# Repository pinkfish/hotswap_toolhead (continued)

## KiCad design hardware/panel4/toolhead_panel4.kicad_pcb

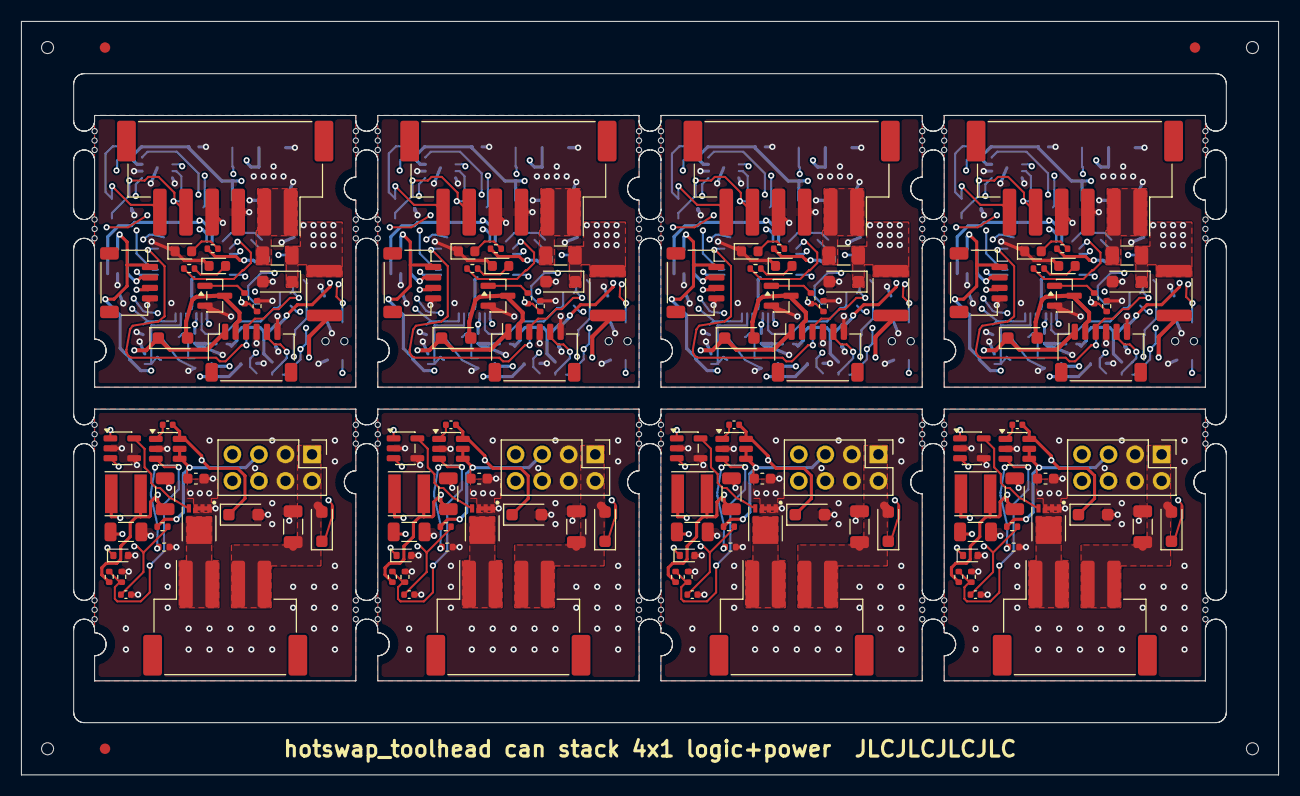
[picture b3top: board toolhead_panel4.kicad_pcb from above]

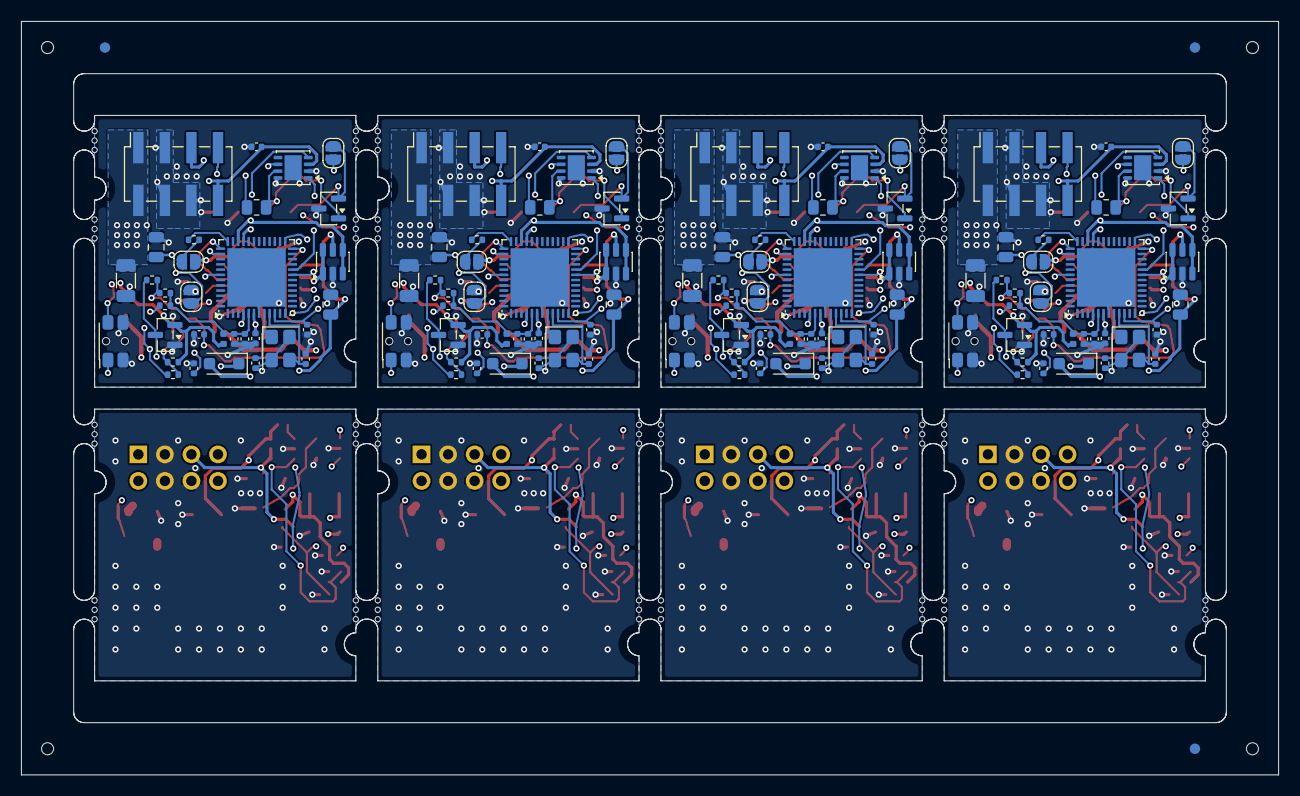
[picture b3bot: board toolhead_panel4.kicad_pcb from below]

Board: 4 copper layers, 120.3 x 72.1 mm, 366 parts (131 on the bottom side), 172 nets.

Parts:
C1_0, C1_2, C1_4, C1_6, C2_1, C2_3, C2_5, C2_7, C4_1, C4_3, C4_5, C4_7: 10uF 50V X5R; C_1206_3216Metric
C5_1, C5_3, C5_5, C5_7: 100nF; C_0603_1608Metric
C6_1, C6_3, C6_5, C6_7, C9_0, C9_2, C9_4, C9_6, C12_0, C12_2, C12_4, C12_6, C15_0, C15_2, C15_4, C15_6, C16_0, C16_2, C16_4, C16_6, C19_0, C19_2, C19_4, C19_6, C20_0, C20_2, C20_4, C20_6: 100nF; C_0402_1005Metric
C8_1, C8_3, C8_5, C8_7: 22uF 25V X5R; C_1206_3216Metric
C10_0, C10_2, C10_4, C10_6, C17_0, C17_2, C17_4, C17_6: 10uF 25V X5R; C_0805_2012Metric
C11_0, C11_2, C11_4, C11_6, C21_1, C21_3, C21_5, C21_7: 1uF; C_0402_1005Metric
C13_0, C13_2, C13_4, C13_6, C14_0, C14_2, C14_4, C14_6: 33pF C0G; C_0402_1005Metric
D1_0, D1_2, D1_4, D1_6: SMF33CA; D_SOD-123F
D3_0, D3_2, D3_4, D3_6, D5_0, D5_2, D5_4, D5_6, D7_1, D7_3, D7_5, D7_7, D9_1, D9_3, D9_5, D9_7: DSK110 100V 1A; D_SOD-123F
D4_0, D4_2, D4_4, D4_6: NUP2105L; SOT-23
D6_0, D6_2, D6_4, D6_6: BAT54S; SOT-23
D10_1, D10_3, D10_5, D10_7: BZX585-C12 12V; D_SOD-523
F1_0, F1_2, F1_4, F1_6: 8A 1206 fuse (0458008.DR); Fuse_1206_3216Metric
F2_0, F2_2, F2_4, F2_6: PTC 0.75A 33V (JK-mSMD075-33); Fuse_1812_4532Metric
FB1_0, FB1_2, FB1_4, FB1_6: 600R@100MHz; L_0402_1005Metric
J1_0, J1_2, J1_4, J1_6: 24V/CAN in (JST XH 1x6 S6B-XH-SM4-TB); JST_XH_S6B-XH-SM4-TB_1x06-1MP_P2.50mm_Horizontal
J2_0, J2_2, J2_4, J2_6: Fan/therm/sensor (JST SH 1x6 SM06B-SRSS-TB); JST_SH_SM06B-SRSS-TB_1x06-1MP_P1.00mm_Horizontal
J3_1, J3_3, J3_5, J3_7: Heater (JST XH 1x4 S4B-XH-SM4-TB); JST_XH_S4B-XH-SM4-TB_1x04-1MP_P2.50mm_Horizontal
J5_0, J5_2, J5_4, J5_6: USB (JST SH 1x4 SM04B-SRSS-TB); JST_SH_SM04B-SRSS-TB_1x04-1MP_P1.00mm_Horizontal
J6_0, J6_2, J6_4, J6_6: Link socket 2x4 (HC-PM254-8.5H-2x4PS); PinSocket_2x04_P2.54mm_Vertical_SMD
J7_1, J7_3, J7_5, J7_7: Link header 2x4 (HX PZ2.54-2x4P ZZ); PinHeader_2x04_P2.54mm_Vertical
JP1_0, JP1_2, JP1_4, JP1_6: TERM; SolderJumper-2_P1.3mm_Open_RoundedPad1.0x1.5mm
JP2_0, JP2_2, JP2_4, JP2_6: NTC/PT1000; SolderJumper-2_P1.3mm_Open_RoundedPad1.0x1.5mm
JP3_0, JP3_2, JP3_4, JP3_6: BOOT; SolderJumper-2_P1.3mm_Open_RoundedPad1.0x1.5mm
KiKit_FID_B_1, KiKit_FID_B_2, KiKit_FID_B_3: Fiducial
KiKit_FID_T_1, KiKit_FID_T_2, KiKit_FID_T_3: Fiducial
KiKit_MB_1_1, KiKit_MB_1_2, KiKit_MB_1_3, KiKit_MB_2_1, KiKit_MB_2_2, KiKit_MB_2_3, KiKit_MB_3_1, KiKit_MB_3_2, KiKit_MB_3_3, KiKit_MB_4_1, KiKit_MB_4_2, KiKit_MB_4_3, KiKit_MB_5_1, KiKit_MB_5_2, KiKit_MB_5_3, KiKit_MB_6_1, KiKit_MB_6_2, KiKit_MB_6_3, KiKit_MB_7_1, KiKit_MB_7_2, KiKit_MB_7_3, KiKit_MB_8_1, KiKit_MB_8_2, KiKit_MB_8_3, KiKit_MB_9_1, KiKit_MB_9_2, KiKit_MB_9_3, KiKit_MB_10_1, KiKit_MB_10_2, KiKit_MB_10_3, KiKit_MB_11_1, KiKit_MB_11_2, KiKit_MB_11_3, KiKit_MB_12_1, KiKit_MB_12_2, KiKit_MB_12_3, KiKit_MB_13_1, KiKit_MB_13_2, KiKit_MB_13_3, KiKit_MB_14_1, KiKit_MB_14_2, KiKit_MB_14_3, KiKit_MB_15_1, KiKit_MB_15_2, KiKit_MB_15_3, KiKit_MB_16_1, KiKit_MB_16_2, KiKit_MB_16_3, KiKit_MB_17_1, KiKit_MB_17_2, KiKit_MB_17_3, KiKit_MB_18_1, KiKit_MB_18_2, KiKit_MB_18_3, KiKit_MB_19_1, KiKit_MB_19_2, KiKit_MB_19_3, KiKit_MB_20_1, KiKit_MB_20_2, KiKit_MB_20_3, KiKit_MB_21_1, KiKit_MB_21_2, KiKit_MB_21_3, KiKit_MB_22_1, KiKit_MB_22_2, KiKit_MB_22_3, KiKit_MB_23_1, KiKit_MB_23_2, KiKit_MB_23_3, KiKit_MB_24_1, KiKit_MB_24_2, KiKit_MB_24_3, KiKit_MB_25_1, KiKit_MB_25_2, KiKit_MB_25_3, KiKit_MB_26_1, KiKit_MB_26_2, KiKit_MB_26_3, KiKit_MB_27_1, KiKit_MB_27_2, KiKit_MB_27_3, KiKit_MB_28_1, KiKit_MB_28_2, KiKit_MB_28_3, KiKit_MB_29_1, KiKit_MB_29_2, KiKit_MB_29_3, KiKit_MB_30_1, KiKit_MB_30_2, KiKit_MB_30_3, KiKit_MB_31_1, KiKit_MB_31_2, KiKit_MB_31_3, KiKit_MB_32_1, KiKit_MB_32_2, KiKit_MB_32_3: NPTH
KiKit_TO_1, KiKit_TO_2, KiKit_TO_3, KiKit_TO_4: NPTH
L1_1, L1_3, L1_5, L1_7: 22uH 1.2A (FNR4030S220MT); L_Taiyo-Yuden_NR-40xx
LED1_0, LED1_2, LED1_4, LED1_6: yellow-green; LED_0603_1608Metric
LED2_0, LED2_2, LED2_4, LED2_6: blue; LED_0603_1608Metric
Q2_1, Q2_3, Q2_5, Q2_7: AON7264E; AOS_DFN-8-1EP_3x3mm_P0.65mm
Q3_0, Q3_2, Q3_4, Q3_6: WST6066A; SOT-23
R2_1, R2_3, R2_5, R2_7: 33k; R_0402_1005Metric
R3_1, R3_3, R3_5, R3_7, R13_1, R13_3, R13_5, R13_7, R14_1, R14_3, R14_5, R14_7, R16_0, R16_2, R16_4, R16_6, R22_0, R22_2, R22_4, R22_6: 10k; R_0402_1005Metric
R4_0, R4_2, R4_4, R4_6, R5_0, R5_2, R5_4, R5_6, R15_0, R15_2, R15_4, R15_6, R19_0, R19_2, R19_4, R19_6, R23_0, R23_2, R23_4, R23_6: 1k; R_0402_1005Metric
R6_0, R6_2, R6_4, R6_6: 100R; R_0402_1005Metric
R11_0, R11_2, R11_4, R11_6: 120R; R_0805_2012Metric
R17_0, R17_2, R17_4, R17_6: 4.7k 0.1% 25ppm; R_0402_1005Metric
R18_0, R18_2, R18_4, R18_6: 4.12k 0.1% 25ppm; R_0402_1005Metric
SW1_0, SW1_2, SW1_4, SW1_6: RESET; SW_SPST_EVQP7C
U1_1, U1_3, U1_5, U1_7: LMR16006XDDC; SOT-23-6
U3_0, U3_2, U3_4, U3_6: TCAN3414DRBR; VSON-8-1EP_3x3mm_P0.65mm_EP1.65x2.4mm
U5_0, U5_2, U5_4, U5_6: USBLC6-2SC6; SOT-23-6
U6_0, U6_2, U6_4, U6_6: STM32G0B1CEU6; QFN-48-1EP_7x7mm_P0.5mm_EP5.6x5.6mm
U7_1, U7_3, U7_5, U7_7: UCC27517DBVR; SOT-23-5
Y1_0, Y1_2, Y1_4, Y1_6: 8MHz 20pF 3225; Crystal_SMD_3225-4Pin_3.2x2.5mm

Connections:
Board_0-/+3V3: C9_0.1, C10_0.1, C16_0.1, D6_0.2 (K2), FB1_0.1, J6_0.8, JP3_0.1, R5_0.1, R22_0.1, U3_0.3, U6_0.4, U6_0.6
Board_0-/+24V: C1_0.1, D1_0.1, F1_0.2, F2_0.1, J6_0.1, J6_0.2
Board_0-/BOOT_SW: JP3_0.2, R4_0.1
Board_0-/CAN_H: D4_0.1, J1_0.5, R11_0.1, U3_0.7
Board_0-/CAN_L: D4_0.2, J1_0.6, JP1_0.2, U3_0.6
Board_0-/CAN_RX: U3_0.4, U6_0.19
Board_0-/CAN_TERM: JP1_0.1, R11_0.2
Board_0-/CAN_TX: U3_0.1, U6_0.20
Board_0-/FAN_G: Q3_0.1, R15_0.2
Board_0-/FAN_N: D5_0.2, J2_0.2, Q3_0.3
Board_0-/FAN_P: D5_0.1, F2_0.2, J2_0.1
Board_0-/FAN_PWM: R15_0.1, R16_0.1, U6_0.25
Board_0-/GND: C1_0.2, C9_0.2, C10_0.2, C11_0.2, C12_0.2, C13_0.2, C14_0.2, C15_0.2, C16_0.2, C17_0.2, C19_0.2, C20_0.2, D1_0.2, D4_0.3, D6_0.1 (A1), J1_0.3, J1_0.4, J2_0.4, J2_0.6, J5_0.4, J6_0.3, J6_0.4, J6_0.6, LED1_0.1 (K), LED2_0.1 (K), Q3_0.2, R16_0.2, SW1_0.2, U3_0.2, U3_0.8, U3_0.9, U5_0.2 (GND), U6_0.7, U6_0.49, Y1_0.2, Y1_0.4
Board_0-/HEAT_PWM: J6_0.7, U6_0.38
Board_0-/JP2_A: JP2_0.2, R18_0.2
Board_0-/LED1_A: LED1_0.2 (A), R5_0.2
Board_0-/LED2_A: LED2_0.2 (A), R6_0.2
Board_0-/LED_STAT: R6_0.1, U6_0.37
Board_0-/NRST: C15_0.1, SW1_0.1, U6_0.10
Board_0-/OSC_IN: C13_0.1, U6_0.8, Y1_0.1
Board_0-/OSC_OUT: C14_0.1, U6_0.9, Y1_0.3
Board_0-/SENS: J2_0.5, R22_0.2, R23_0.1
Board_0-/SENS_IN: C20_0.1, R23_0.2, U6_0.42
Board_0-/SWCLK: R4_0.2, U6_0.36
Board_0-/TH_ADC: C19_0.1, D6_0.3 (K1/A2), R19_0.2, U6_0.24
Board_0-/TH_SIG: J2_0.3, JP2_0.1, R17_0.2, R19_0.1
Board_0-/USB_D_N: J5_0.2, U5_0.1 (IO1), U5_0.6 (IO1), U6_0.33
Board_0-/USB_D_P: J5_0.3, U5_0.3 (IO2), U5_0.4 (IO2), U6_0.34
Board_0-/VBUS: C17_0.1, D3_0.2, J5_0.1, U5_0.5 (VBUS)
Board_0-/VIN_LOGIC: D3_0.1, J6_0.5
Board_0-/VIN_RAW: F1_0.1, J1_0.1, J1_0.2
Board_0-/VREFP: C11_0.1, C12_0.1, FB1_0.2, R17_0.1, R18_0.1, U6_0.5
Board_1-/+3V3: C8_1.1, J7_1.8, L1_1.2, R2_1.1
Board_1-/+24V: C2_1.1, D7_1.2, J3_1.3, J3_1.4, J7_1.1, J7_1.2
Board_1-/BUCK_BOOT: C6_1.1, U1_1.1
Board_1-/BUCK_FB: R2_1.2, R3_1.1, U1_1.3
Board_1-/BUCK_SW: C6_1.2, D9_1.1, L1_1.1, U1_1.6
Board_1-/GATE_12V: C21_1.1, D10_1.1, R13_1.2, U7_1.1
Board_1-/GND: C2_1.2, C4_1.2, C5_1.2, C8_1.2, C21_1.2, D9_1.2, D10_1.2, J7_1.3, J7_1.4, J7_1.6, Q2_1.1, Q2_1.2, Q2_1.3, R3_1.2, R14_1.2, U1_1.2, U7_1.2, U7_1.4
Board_1-/HEAT_G: Q2_1.4, U7_1.5
Board_1-/HEAT_N: J3_1.1, J3_1.2, Q2_1.5
Board_1-/HEAT_PWM: J7_1.7, R14_1.1, U7_1.3
Board_1-/VIN_LOGIC: C4_1.1, C5_1.1, D7_1.1, J7_1.5, R13_1.1, U1_1.4, U1_1.5
Board_2-/+3V3: C9_2.1, C10_2.1, C16_2.1, D6_2.2 (K2), FB1_2.1, J6_2.8, JP3_2.1, R5_2.1, R22_2.1, U3_2.3, U6_2.4, U6_2.6
Board_2-/+24V: C1_2.1, D1_2.1, F1_2.2, F2_2.1, J6_2.1, J6_2.2
Board_2-/BOOT_SW: JP3_2.2, R4_2.1
Board_2-/CAN_H: D4_2.1, J1_2.5, R11_2.1, U3_2.7
Board_2-/CAN_L: D4_2.2, J1_2.6, JP1_2.2, U3_2.6
Board_2-/CAN_RX: U3_2.4, U6_2.19
Board_2-/CAN_TERM: JP1_2.1, R11_2.2
Board_2-/CAN_TX: U3_2.1, U6_2.20
Board_2-/FAN_G: Q3_2.1, R15_2.2
Board_2-/FAN_N: D5_2.2, J2_2.2, Q3_2.3
Board_2-/FAN_P: D5_2.1, F2_2.2, J2_2.1
Board_2-/FAN_PWM: R15_2.1, R16_2.1, U6_2.25
Board_2-/GND: C1_2.2, C9_2.2, C10_2.2, C11_2.2, C12_2.2, C13_2.2, C14_2.2, C15_2.2, C16_2.2, C17_2.2, C19_2.2, C20_2.2, D1_2.2, D4_2.3, D6_2.1 (A1), J1_2.3, J1_2.4, J2_2.4, J2_2.6, J5_2.4, J6_2.3, J6_2.4, J6_2.6, LED1_2.1 (K), LED2_2.1 (K), Q3_2.2, R16_2.2, SW1_2.2, U3_2.2, U3_2.8, U3_2.9, U5_2.2 (GND), U6_2.7, U6_2.49, Y1_2.2, Y1_2.4
Board_2-/HEAT_PWM: J6_2.7, U6_2.38
Board_2-/JP2_A: JP2_2.2, R18_2.2
Board_2-/LED1_A: LED1_2.2 (A), R5_2.2
Board_2-/LED2_A: LED2_2.2 (A), R6_2.2
Board_2-/LED_STAT: R6_2.1, U6_2.37
Board_2-/NRST: C15_2.1, SW1_2.1, U6_2.10
Board_2-/OSC_IN: C13_2.1, U6_2.8, Y1_2.1
Board_2-/OSC_OUT: C14_2.1, U6_2.9, Y1_2.3
Board_2-/SENS: J2_2.5, R22_2.2, R23_2.1
Board_2-/SENS_IN: C20_2.1, R23_2.2, U6_2.42
Board_2-/SWCLK: R4_2.2, U6_2.36
Board_2-/TH_ADC: C19_2.1, D6_2.3 (K1/A2), R19_2.2, U6_2.24
Board_2-/TH_SIG: J2_2.3, JP2_2.1, R17_2.2, R19_2.1
Board_2-/USB_D_N: J5_2.2, U5_2.1 (IO1), U5_2.6 (IO1), U6_2.33
Board_2-/USB_D_P: J5_2.3, U5_2.3 (IO2), U5_2.4 (IO2), U6_2.34
Board_2-/VBUS: C17_2.1, D3_2.2, J5_2.1, U5_2.5 (VBUS)
Board_2-/VIN_LOGIC: D3_2.1, J6_2.5
Board_2-/VIN_RAW: F1_2.1, J1_2.1, J1_2.2
Board_2-/VREFP: C11_2.1, C12_2.1, FB1_2.2, R17_2.1, R18_2.1, U6_2.5
Board_3-/+3V3: C8_3.1, J7_3.8, L1_3.2, R2_3.1
Board_3-/+24V: C2_3.1, D7_3.2, J3_3.3, J3_3.4, J7_3.1, J7_3.2
Board_3-/BUCK_BOOT: C6_3.1, U1_3.1
Board_3-/BUCK_FB: R2_3.2, R3_3.1, U1_3.3
Board_3-/BUCK_SW: C6_3.2, D9_3.1, L1_3.1, U1_3.6
Board_3-/GATE_12V: C21_3.1, D10_3.1, R13_3.2, U7_3.1
Board_3-/GND: C2_3.2, C4_3.2, C5_3.2, C8_3.2, C21_3.2, D9_3.2, D10_3.2, J7_3.3, J7_3.4, J7_3.6, Q2_3.1, Q2_3.2, Q2_3.3, R3_3.2, R14_3.2, U1_3.2, U7_3.2, U7_3.4
Board_3-/HEAT_G: Q2_3.4, U7_3.5
Board_3-/HEAT_N: J3_3.1, J3_3.2, Q2_3.5
Board_3-/HEAT_PWM: J7_3.7, R14_3.1, U7_3.3
Board_3-/VIN_LOGIC: C4_3.1, C5_3.1, D7_3.1, J7_3.5, R13_3.1, U1_3.4, U1_3.5
Board_4-/+3V3: C9_4.1, C10_4.1, C16_4.1, D6_4.2 (K2), FB1_4.1, J6_4.8, JP3_4.1, R5_4.1, R22_4.1, U3_4.3, U6_4.4, U6_4.6
Board_4-/+24V: C1_4.1, D1_4.1, F1_4.2, F2_4.1, J6_4.1, J6_4.2
Board_4-/BOOT_SW: JP3_4.2, R4_4.1
Board_4-/CAN_H: D4_4.1, J1_4.5, R11_4.1, U3_4.7
Board_4-/CAN_L: D4_4.2, J1_4.6, JP1_4.2, U3_4.6
Board_4-/CAN_RX: U3_4.4, U6_4.19
Board_4-/CAN_TERM: JP1_4.1, R11_4.2
Board_4-/CAN_TX: U3_4.1, U6_4.20
Board_4-/FAN_G: Q3_4.1, R15_4.2
Board_4-/FAN_N: D5_4.2, J2_4.2, Q3_4.3
Board_4-/FAN_P: D5_4.1, F2_4.2, J2_4.1
Board_4-/FAN_PWM: R15_4.1, R16_4.1, U6_4.25
Board_4-/GND: C1_4.2, C9_4.2, C10_4.2, C11_4.2, C12_4.2, C13_4.2, C14_4.2, C15_4.2, C16_4.2, C17_4.2, C19_4.2, C20_4.2, D1_4.2, D4_4.3, D6_4.1 (A1), J1_4.3, J1_4.4, J2_4.4, J2_4.6, J5_4.4, J6_4.3, J6_4.4, J6_4.6, LED1_4.1 (K), LED2_4.1 (K), Q3_4.2, R16_4.2, SW1_4.2, U3_4.2, U3_4.8, U3_4.9, U5_4.2 (GND), U6_4.7, U6_4.49, Y1_4.2, Y1_4.4
Board_4-/HEAT_PWM: J6_4.7, U6_4.38
Board_4-/JP2_A: JP2_4.2, R18_4.2
Board_4-/LED1_A: LED1_4.2 (A), R5_4.2
Board_4-/LED2_A: LED2_4.2 (A), R6_4.2
Board_4-/LED_STAT: R6_4.1, U6_4.37
Board_4-/NRST: C15_4.1, SW1_4.1, U6_4.10
Board_4-/OSC_IN: C13_4.1, U6_4.8, Y1_4.1
Board_4-/OSC_OUT: C14_4.1, U6_4.9, Y1_4.3
Board_4-/SENS: J2_4.5, R22_4.2, R23_4.1
Board_4-/SENS_IN: C20_4.1, R23_4.2, U6_4.42
Board_4-/SWCLK: R4_4.2, U6_4.36
Board_4-/TH_ADC: C19_4.1, D6_4.3 (K1/A2), R19_4.2, U6_4.24
Board_4-/TH_SIG: J2_4.3, JP2_4.1, R17_4.2, R19_4.1
Board_4-/USB_D_N: J5_4.2, U5_4.1 (IO1), U5_4.6 (IO1), U6_4.33
Board_4-/USB_D_P: J5_4.3, U5_4.3 (IO2), U5_4.4 (IO2), U6_4.34
Board_4-/VBUS: C17_4.1, D3_4.2, J5_4.1, U5_4.5 (VBUS)
Board_4-/VIN_LOGIC: D3_4.1, J6_4.5
Board_4-/VIN_RAW: F1_4.1, J1_4.1, J1_4.2
Board_4-/VREFP: C11_4.1, C12_4.1, FB1_4.2, R17_4.1, R18_4.1, U6_4.5
Board_5-/+3V3: C8_5.1, J7_5.8, L1_5.2, R2_5.1
Board_5-/+24V: C2_5.1, D7_5.2, J3_5.3, J3_5.4, J7_5.1, J7_5.2
Board_5-/BUCK_BOOT: C6_5.1, U1_5.1
Board_5-/BUCK_FB: R2_5.2, R3_5.1, U1_5.3
Board_5-/BUCK_SW: C6_5.2, D9_5.1, L1_5.1, U1_5.6
Board_5-/GATE_12V: C21_5.1, D10_5.1, R13_5.2, U7_5.1
Board_5-/GND: C2_5.2, C4_5.2, C5_5.2, C8_5.2, C21_5.2, D9_5.2, D10_5.2, J7_5.3, J7_5.4, J7_5.6, Q2_5.1, Q2_5.2, Q2_5.3, R3_5.2, R14_5.2, U1_5.2, U7_5.2, U7_5.4
Board_5-/HEAT_G: Q2_5.4, U7_5.5
Board_5-/HEAT_N: J3_5.1, J3_5.2, Q2_5.5
Board_5-/HEAT_PWM: J7_5.7, R14_5.1, U7_5.3
Board_5-/VIN_LOGIC: C4_5.1, C5_5.1, D7_5.1, J7_5.5, R13_5.1, U1_5.4, U1_5.5
Board_6-/+3V3: C9_6.1, C10_6.1, C16_6.1, D6_6.2 (K2), FB1_6.1, J6_6.8, JP3_6.1, R5_6.1, R22_6.1, U3_6.3, U6_6.4, U6_6.6
Board_6-/+24V: C1_6.1, D1_6.1, F1_6.2, F2_6.1, J6_6.1, J6_6.2
Board_6-/BOOT_SW: JP3_6.2, R4_6.1
Board_6-/CAN_H: D4_6.1, J1_6.5, R11_6.1, U3_6.7
Board_6-/CAN_L: D4_6.2, J1_6.6, JP1_6.2, U3_6.6
Board_6-/CAN_RX: U3_6.4, U6_6.19
Board_6-/CAN_TERM: JP1_6.1, R11_6.2
Board_6-/CAN_TX: U3_6.1, U6_6.20
Board_6-/FAN_G: Q3_6.1, R15_6.2
Board_6-/FAN_N: D5_6.2, J2_6.2, Q3_6.3
Board_6-/FAN_P: D5_6.1, F2_6.2, J2_6.1
Board_6-/FAN_PWM: R15_6.1, R16_6.1, U6_6.25
Board_6-/GND: C1_6.2, C9_6.2, C10_6.2, C11_6.2, C12_6.2, C13_6.2, C14_6.2, C15_6.2, C16_6.2, C17_6.2, C19_6.2, C20_6.2, D1_6.2, D4_6.3, D6_6.1 (A1), J1_6.3, J1_6.4, J2_6.4, J2_6.6, J5_6.4, J6_6.3, J6_6.4, J6_6.6, LED1_6.1 (K), LED2_6.1 (K), Q3_6.2, R16_6.2, SW1_6.2, U3_6.2, U3_6.8, U3_6.9, U5_6.2 (GND), U6_6.7, U6_6.49, Y1_6.2, Y1_6.4
Board_6-/HEAT_PWM: J6_6.7, U6_6.38
Board_6-/JP2_A: JP2_6.2, R18_6.2
Board_6-/LED1_A: LED1_6.2 (A), R5_6.2
Board_6-/LED2_A: LED2_6.2 (A), R6_6.2
Board_6-/LED_STAT: R6_6.1, U6_6.37
Board_6-/NRST: C15_6.1, SW1_6.1, U6_6.10
Board_6-/OSC_IN: C13_6.1, U6_6.8, Y1_6.1
Board_6-/OSC_OUT: C14_6.1, U6_6.9, Y1_6.3
Board_6-/SENS: J2_6.5, R22_6.2, R23_6.1
Board_6-/SENS_IN: C20_6.1, R23_6.2, U6_6.42
Board_6-/SWCLK: R4_6.2, U6_6.36
Board_6-/TH_ADC: C19_6.1, D6_6.3 (K1/A2), R19_6.2, U6_6.24
Board_6-/TH_SIG: J2_6.3, JP2_6.1, R17_6.2, R19_6.1
Board_6-/USB_D_N: J5_6.2, U5_6.1 (IO1), U5_6.6 (IO1), U6_6.33
Board_6-/USB_D_P: J5_6.3, U5_6.3 (IO2), U5_6.4 (IO2), U6_6.34
Board_6-/VBUS: C17_6.1, D3_6.2, J5_6.1, U5_6.5 (VBUS)
Board_6-/VIN_LOGIC: D3_6.1, J6_6.5
Board_6-/VIN_RAW: F1_6.1, J1_6.1, J1_6.2
Board_6-/VREFP: C11_6.1, C12_6.1, FB1_6.2, R17_6.1, R18_6.1, U6_6.5
Board_7-/+3V3: C8_7.1, J7_7.8, L1_7.2, R2_7.1
Board_7-/+24V: C2_7.1, D7_7.2, J3_7.3, J3_7.4, J7_7.1, J7_7.2
Board_7-/BUCK_BOOT: C6_7.1, U1_7.1
Board_7-/BUCK_FB: R2_7.2, R3_7.1, U1_7.3
Board_7-/BUCK_SW: C6_7.2, D9_7.1, L1_7.1, U1_7.6
Board_7-/GATE_12V: C21_7.1, D10_7.1, R13_7.2, U7_7.1
Board_7-/GND: C2_7.2, C4_7.2, C5_7.2, C8_7.2, C21_7.2, D9_7.2, D10_7.2, J7_7.3, J7_7.4, J7_7.6, Q2_7.1, Q2_7.2, Q2_7.3, R3_7.2, R14_7.2, U1_7.2, U7_7.2, U7_7.4
Board_7-/HEAT_G: Q2_7.4, U7_7.5
Board_7-/HEAT_N: J3_7.1, J3_7.2, Q2_7.5
Board_7-/HEAT_PWM: J7_7.7, R14_7.1, U7_7.3
Board_7-/VIN_LOGIC: C4_7.1, C5_7.1, D7_7.1, J7_7.5, R13_7.1, U1_7.4, U1_7.5

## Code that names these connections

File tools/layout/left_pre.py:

"""left_pre.py board.kicad_pcb - pre-route the lines leaving U6's left side, on B.Cu.
TH_ADC (pin 13) and SENS_IN (pin 14) leave side by side and run down parallel lanes past
the crystal cluster, TH_ADC inside, so they never cross:
- TH_ADC drops beside C15/C14 to R19, picks up C19 next to it and, through one via, the
  D6 clamp on top: the filter and clamp stay within a few mm of the pin
- SENS_IN drops one lane further out, turns west under C16 and comes up through a via
  under C20, the switch input's filter cap on top
CAN_TX/CAN_RX run in two more lanes outside SENS_IN's, down past U3's pin column, and
U3's +3V3 pin, boxed in by the CAN lanes, is fed through a via beside it. FAN_PWM
crosses the lanes on F.Cu just below JP1, so U3's CAN pins stay clear.
Runs before planes_fanout so the plane vias land clear of all of these.
"""
import sys

import pcbnew

mm = pcbnew.FromMM
b = pcbnew.LoadBoard(sys.argv[1])
O = 100.0
FP = {f.GetReference(): f for f in b.GetFootprints()}
F, B = pcbnew.F_Cu, pcbnew.B_Cu


def at(ref, num):
    q = [p for p in FP[ref].Pads() if p.GetNumber() == num][0].GetPosition()
    return pcbnew.ToMM(q.x) - O, pcbnew.ToMM(q.y) - O


def pad_net(ref, net):
    p = [p for p in FP[ref].Pads() if p.GetNetname() == net][0].GetPosition()
    return pcbnew.ToMM(p.x) - O, pcbnew.ToMM(p.y) - O


def route(net, layer, *pts):
    for a, c in zip(pts, pts[1:]):
        t = pcbnew.PCB_TRACK(b)
        t.SetStart(pcbnew.VECTOR2I(mm(O + a[0]), mm(O + a[1])))
        t.SetEnd(pcbnew.VECTOR2I(mm(O + c[0]), mm(O + c[1])))
        t.SetWidth(mm(0.2))
        t.SetLayer(layer)
        t.SetNet(b.FindNet(net))
        t.SetLocked(True)
        b.Add(t)


def via(net, x, y):
    v = pcbnew.PCB_VIA(b)
    v.SetPosition(pcbnew.VECTOR2I(mm(O + x), mm(O + y)))
    v.SetWidth(mm(0.6))
    v.SetDrill(mm(0.3))
    v.SetNet(b.FindNet(net))
    v.SetLocked(True)
    b.Add(v)


th, sens = at('U6', '13'), at('U6', '14')
r19, c19, d6 = pad_net('R19', '/TH_ADC'), pad_net('C19', '/TH_ADC'), pad_net('D6', '/TH_ADC')
c20 = pad_net('C20', '/SENS_IN')
# TH_ADC: lane 0.45 mm left of C15's pads, down to R19, C19 alongside, via up to D6
xt = pad_net('C15', '/NRST')[0] - 0.75
route('/TH_ADC', B, th, (xt, th[1]), (xt, r19[1] - 0.6), r19, c19)
vy = d6[1] - 0.75
via('/TH_ADC', xt, vy)
route('/TH_ADC', F, (xt, vy), (xt, d6[1]), d6)
# SENS_IN: lane 0.6 mm further out, west between C16 and C19, up under C20
xs, ys = xt - 0.6, r19[1] - 0.75
xv = c20[0] + 1.6
route('/SENS_IN', B, sens, (xs, sens[1]), (xs, ys), (xv, ys))
via('/SENS_IN', xv, ys)
route('/SENS_IN', F, (xv, ys), (c20[0], ys), c20)
# CAN_TX / CAN_RX: straight across from pins 20/19 and down two lanes between U3's pin
# column and SENS_IN's, TX inside to U3 pin 1, RX outside to pin 4 at the bottom
tx, rx = at('U6', '20'), at('U6', '19')
u3tx, u3rx = pad_net('U3', '/CAN_TX'), pad_net('U3', '/CAN_RX')
xtx, xrx = u3tx[0] + 0.25, xs - 0.55
route('/CAN_TX', B, tx, (xtx, tx[1]), (xtx, u3tx[1] - 0.45), u3tx)
route('/CAN_RX', B, rx, (xrx, rx[1]), (xrx, u3rx[1]), u3rx)          # level with pin 4, clear of pin 3
# +3V3 for U3 pin 3, which sits inside the CAN_TX/CAN_RX loop: a via beside the pin, then
# F.Cu round to D6's +3V3 pad, with a second via down to C16, U3's decoupling cap
p3 = pad_net('U3', '/+3V3')
p3r = max(pcbnew.ToMM(p.GetBoundingBox().GetRight()) for p in FP['U3'].Pads() if p.GetNetname() == '/+3V3') - O
c16, d6v = pad_net('C16', '/+3V3'), pad_net('D6', '/+3V3')
lv = (p3r + 0.51, p3[1])
xt3 = c16[0] + 0.18
route('/+3V3', B, p3, lv)
via('/+3V3', *lv)
route('/+3V3', F, lv, (xt3, lv[1]), (xt3, c16[1] - 0.75), (xt3, d6v[1]), d6v)
via('/+3V3', xt3, c16[1] - 0.75)
route('/+3V3', B, (xt3, c16[1] - 0.75), c16)
# CAN_H / CAN_L at U3: pins 6/7 face H1's keep-out, with one track's width between them,
# and pin 8 (GND) above them. Pins 8 and 2 tie into the exposed pad instead of taking a via;
# CAN_H takes the corridor up and across under D4 to its pad 1, and CAN_L drops through a
# via below pin 5 and runs up on F.Cu to JP1, with a second via down to D4 pad 2
ep = [p for p in FP['U3'].Pads() if p.GetNumber() == ''][0].GetBoundingBox()
epl, epr = pcbnew.ToMM(ep.GetLeft()) - O, pcbnew.ToMM(ep.GetRight()) - O
g8, g2 = at('U3', '8'), at('U3', '2')
route('/GND', B, g8, (epl + 0.2, g8[1]))
route('/GND', B, g2, (epr - 0.2, g2[1]))
ec = ((epl + epr) / 2, pcbnew.ToMM(ep.GetCenter().y) - O)
via('/GND', ec[0] - 0.15, ec[1] + 0.7)    # the pad's plane via, clear of FAN_PWM and the +3V3 feed on top
ch, cl = at('U3', '7'), at('U3', '6')
d4h, d4l, jl2 = pad_net('D4', '/CAN_H'), pad_net('D4', '/CAN_L'), pad_net('JP1', '/CAN_L')
xc = ch[0] - 0.76                          # corridor between the pins and H1's keep-out
yh = d4h[1] + 1.21                         # under D4's pads, above pin 8
route('/CAN_H', B, ch, (xc, ch[1]), (xc, yh), (d4h[0], yh), d4h)
v1 = (xc + 0.11, cl[1] + 1.42)             # below pin 5, clear of C20 on top
route('/CAN_L', B, cl, (xc, cl[1]), (xc, v1[1] - 0.35), v1)
via('/CAN_L', *v1)
v2 = (xc + 0.46, d4l[1] + 0.06)            # beside D4 pad 2
route('/CAN_L', F, v1, (v1[0], jl2[1] + 0.35), (v2[0], jl2[1]), jl2)
route('/CAN_L', F, (v2[0], jl2[1]), v2)
via('/CAN_L', *v2)
route('/CAN_L', B, v2, d4l)
# FAN_PWM: pin 17 sits between the CAN_RX and SENS_IN lanes, which wall U6 off from the
# west on B.Cu. A via just off the pin, then F.Cu down the gap between C1's pads, west under
# C1 and JP1 (crossing all four lanes), down between JP1 and CAN_L's F.Cu run, and west
# above Q3 to R15/R16
fp = at('U6', '17')
r15, r16 = pad_net('R15', '/FAN_PWM'), pad_net('R16', '/FAN_PWM')
c1r = pcbnew.ToMM([p for p in FP['C1'].Pads() if p.GetNetname() == '/+24V'][0].GetBoundingBox().GetRight()) - O
jp = [p.GetBoundingBox() for p in FP['JP1'].Pads()]
jl, jr = (min(pcbnew.ToMM(r.GetLeft()) for r in jp) - O, max(pcbnew.ToMM(r.GetRight()) for r in jp) - O)
jb = max(pcbnew.ToMM(r.GetBottom()) for r in jp) - O
qt = min(pcbnew.ToMM(p.GetBoundingBox().GetTop()) for p in FP['Q3'].Pads()) - O
vf = (fp[0] - 1.06, fp[1] - 0.35)          # 0.3 mm from C1's 24 V pad above, CAN_RX's lane below
xg, y1, xw, yl = c1r + 0.45, jb + 0.3, jl - 0.55, qt - 0.5
route('/FAN_PWM', B, fp, (fp[0] - 0.71, fp[1]), vf)
via('/FAN_PWM', *vf)
route('/FAN_PWM', F, vf, (xg, vf[1]), (xg, y1 - 0.17), (jr + 0.25, y1 - 0.17), (jr + 0.05, y1), (xw, y1), (xw, yl),
      (r15[0] + 1.6, yl), (r15[0] + 1.45, yl - 0.1), (r15[0], yl - 0.1), r15, r16)
pcbnew.SaveBoard(sys.argv[1], b)
print('TH_ADC, SENS_IN, CAN_TX/RX, the U3 CAN_H/CAN_L escape, U3 +3V3 and FAN_PWM pre-routed')

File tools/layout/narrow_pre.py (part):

"""narrow_pre.py board.kicad_pcb - pre-routes for the 27 mm board (run_narrow.sh).
FAN_P: F2's output reaches the fan clamp D5, under J2, round the right-hand end of J2's pin rows: down
from F2 pad 2 on F.Cu to a via right of J2 pin 1, then on B.Cu down the lane between J2's pins
and L1 and across to D5 pad 1. The 31 mm board's via was where Q2 now is; between J2's pins
there's no room (0.8 mm gaps), and the HEAT_N pour takes the lane on top.
D7's +24V via: up-left of its pad as on the 31 mm board (BUCK_FB runs between D7's pads, and
U6 pin 48's escape takes the room below), replacing the block copper's.
LED_STAT: from U6 pin 44 up to a via above D7's, then on F.Cu down its left to R6.
HEAT_PWM, NRST: kept from crossing east of U6 (U7 is below that, SW1 above); NRST above C8.
VREFP: out of its decoupling to the right and back left on F.Cu between C8 and F2.
LED1_A, LED2_A: R6 left, R5 right, so the anodes go up the right of the LEDs without crossing;
R5's +3V3 up the right of LED1's lane to a via above LED1, then on B.Cu to R2.
F2's +24V: a plane via below pad 1, between Y1 and J2's pins.
FAN_PWM: round the CAN pair to R15, along the strip below J1 (CAN_L drops to B.Cu above it).
CAN_L: D4 to U3's pin 6 down U3's left.
"""
import sys

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route(F, f2a, (f2a[0], vf[1] - 0.34), vf, net='/+24V', w=0.8)
via('/+24V', vf, 0.8, 0.4)

# HEAT_PWM and NRST, which would cross east of U6: HEAT_PWM from pin 48 on B.Cu to a via below R6,
# clear of D7 and U1, then on F.Cu down to U7; NRST above C8 and under the LED resistors to SW1
for t in list(b.GetTracks()):
    if t.GetNetname() == '/HEAT_PWM':
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route(F, v1, (v1[0] + 0.35, v1[1] + 0.35), (v1[0] + 0.35, v2[1] - 1.5), v2, net='/+3V3', w=0.25)
route(B, v2, (v2[0] + 0.2, v2[1] + 0.2), (l12[0], v2[1] + 0.2), l12, net='/+3V3', w=0.25)

# FAN_PWM to R15 on the left edge has to cross the CAN pair coming down from J1: from U6 pin 17
# on B.Cu to a via left of C1, then on F.Cu up and along the strip below J1 to R15. CAN_L drops
# to B.Cu at the end of its F.Cu run from J1, above the strip, so the two don't cross on F.Cu.
p17, r15 = at('U6', '17'), at('R15', '1')
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          if t.GetNetname() == '/CAN_L' and t.GetLayer() == F and t.GetClass() == 'PCB_TRACK'
          and pcbnew.ToMM(min(t.GetStart().x, t.GetEnd().x)) - O < 4), key=lambda q: q.y)
via('/CAN_L', (pcbnew.ToMM(cl.x) - O, pcbnew.ToMM(cl.y) - O))
# CAN_L from D4 down the left of U3 to its pin 6 (the routers left it boxed in by CAN_H and the fan)
u36, d42 = at('U3', '6'), at('D4', '2')
route(B, u36, (u36[0] - 0.76, u36[1]), (u36[0] - 1.2, u36[1] - 0.44), (u36[0] - 1.2, u36[1] - 2.3),
      (u36[0] - 0.95, u36[1] - 2.5), (d42[0] - 0.25, u36[1] - 2.8), d42, net='/CAN_L', w=0.2)
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
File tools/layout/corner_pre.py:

"""Hand layout of the U6 pin 4-10 corner (crystal, load caps, decoupling, VREF), before routing.
    corner_pre.py board.kicad_pcb
Same cluster as rev A's routed board, shifted with U6: parts placed with pad 1 up/down,
+3V3 pins 4 and 6 dropped to staggered vias so VREFP (pin 5) runs straight down between
them, and GND pin 7 tied into the exposed pad. VREFP's long run to R17 starts here too.
"""
import sys

import pcbnew

mm = pcbnew.FromMM
b = pcbnew.LoadBoard(sys.argv[1])
OX = OY = 100.0
FP = {f.GetReference(): f for f in b.GetFootprints()}
u6 = FP['U6']
DX = pcbnew.ToMM(u6.GetPosition().x) - OX - 16.3
DY = pcbnew.ToMM(u6.GetPosition().y) - OY - 23.6
PLACE = {
    'Y1': (14.0, 30.4, 270),
    'C9': (16.4, 29.43, 'up'),
    'C11': (17.42, 29.48, 'up'),
    'C12': (18.44, 29.48, 'up'),
    'FB1': (19.46, 29.48, 'down'),     # pad 2 (VREFP) on top, in line with C11/C12
    'C13': (16.4, 31.8, 'up'),
    'C14': (11.6, 31.4, 'down'),       # GND pad up, so it can tie to C15's (TH_ADC boxes it in below)
    'C15': (11.45, 28.6, 'up'),        # 0.3 right of rev A: opens the TH_ADC lane by J2
}
PIN_VIAS = {'6': (16.4, 28.2), '4': (17.75, 28.15)}
KNEE_Y = 27.6


def P(x, y):
    return pcbnew.VECTOR2I(mm(OX + x + DX), mm(OY + y + DY))


def pad(f, n):
    return [p for p in f.Pads() if p.GetNumber() == n][0]


def track(net, a, c, w):
    t = pcbnew.PCB_TRACK(b)
    t.SetStart(a)
    t.SetEnd(c)
    t.SetWidth(mm(w))
    t.SetLayer(pcbnew.B_Cu)
    t.SetNet(net)
    t.SetLocked(True)
    b.Add(t)


for ref, (x, y, rot) in PLACE.items():
    f = FP[ref]
    f.SetPosition(P(x, y))
    if rot in ('up', 'down'):
        best = None
        for a in (0, 90, 180, 270):
            f.SetOrientationDegrees(a)
            key = pad(f, '1').GetPosition().y * (1 if rot == 'up' else -1)
            if best is None or key < best[0]:
                best = (key, a)
        rot = best[1]
    f.SetOrientationDegrees(rot)

p7, ep = pad(u6, '7'), pad(u6, '49')
c7 = p7.GetPosition()
track(p7.GetNet(), c7, pcbnew.VECTOR2I(c7.x, ep.GetBoundingBox().GetBottom() - mm(0.2)), 0.2)
for num, (x, y) in PIN_VIAS.items():
    p = pad(u6, num)
    pos = P(x, y)
    knee = pcbnew.VECTOR2I(p.GetPosition().x, P(0, KNEE_Y).y)
    track(p.GetNet(), p.GetPosition(), knee, 0.25)
    track(p.GetNet(), knee, pos, 0.25)
    v = pcbnew.PCB_VIA(b)
    v.SetPosition(pos)
    v.SetWidth(mm(0.6))
    v.SetDrill(mm(0.3))
    v.SetNet(p.GetNet())
    v.SetLocked(True)
    b.Add(v)
# U6 pins 8-10 (OSC_IN, OSC_OUT, NRST) pre-routed so none boxes another in: NRST hugs the
# pin row out to C15, OSC_OUT runs under it and round the left of Y1's GND pad 4 to pad 3
# and C14, OSC_IN drops straight to Y1 pad 1 and on down the right side to C13.  Pad 4 is
# then enclosed, so it ties diagonally across the crystal to GND pad 2.
y1 = FP['Y1']


def R(*pts, net, w=0.2):
    pts = [pcbnew.VECTOR2I(mm(OX + x), mm(OY + y)) for x, y in pts]
    for a, c in zip(pts, pts[1:]):
        track(b.FindNet(net), a, c, w)


def at(f, n):
    q = pad(f, n).GetPosition()
    return pcbnew.ToMM(q.x) - OX, pcbnew.ToMM(q.y) - OY


def box(f, n):
    r = pad(f, n).GetBoundingBox()
    return [pcbnew.ToMM(v) - o for v, o in ((r.GetX(), OX), (r.GetY(), OY), (r.GetRight(), OX), (r.GetBottom(), OY))]


x8, yp = at(u6, '8')
x9, _ = at(u6, '9')
x10, _ = at(u6, '10')
row = box(u6, '9')[3]                      # pin row bottom edge
c15, c14, c13 = at(FP['C15'], '1'), at(FP['C14'], '1'), at(FP['C13'], '1')
p4 = box(y1, '4')                          # GND pad nearest the pins, left
p1 = box(y1, '1')                          # OSC_IN pad, right
q3 = at(y1, '3')
xl = p4[0] - 0.33
yo = row + 0.72
R((x10, yp), (x10, row + 0.32), (c15[0] + 0.35, row + 0.32), c15, net='/NRST')
R((x9, yp), (x9, yo), (xl, yo), (xl, c14[1]), c14, net='/OSC_OUT')
R((xl, c14[1]), (q3[0] - 0.35, q3[1] - 0.3), net='/OSC_OUT')
xr = p1[2] + 0.3
R((x8, yp), (x8, p1[1] + 0.2), (p1[2] - 0.25, p1[1] + 0.4), net='/OSC_IN')
R((x8, p1[1] + 0.2), (xr, p1[1] + 0.4), (xr, c13[1]), c13, net='/OSC_IN')
R(at(y1, '4'), at(y1, '2'), net='/GND')
# TH_ADC's lane (left_pre) closes off the GND pads under the crystal: tie them to neighbours with vias
R(at(FP['C14'], '2'), at(FP['C15'], '2'), net='/GND')
g = at(FP['C14'], '2'); g = (g[0] - 0.1, g[1] - 0.35)   # that pair is boxed in too: via on C14's pad edge, clear of TH_ADC's via and D6
gv = pcbnew.PCB_VIA(b)
gv.SetPosition(pcbnew.VECTOR2I(mm(OX + g[0]), mm(OY + g[1])))
gv.SetWidth(mm(0.6))
gv.SetDrill(mm(0.3))
gv.SetNet(b.FindNet('/GND'))
gv.SetLocked(True)
b.Add(gv)
R(at(y1, '2'), at(FP['C13'], '2'), net='/GND')
# VREFP's exit towards the thermistor pull-up (R17, far left): the C11/C12/FB1 row is closed
# in above by the pin vias and below by the GND/+3V3 pads, so it leaves round the east side
# of FB1 and drops on B.Cu to below the row; the router takes it on from there
fb, f1 = at(FP['FB1'], '2'), box(FP['FB1'], '1')
xe = f1[2] + 0.36
R(fb, (xe, fb[1]), (xe, f1[3] + 0.13), (fb[0] + 0.14, f1[3] + 0.54), (fb[0] + 0.14, f1[3] + 1.2), net='/VREFP')
# that loop closes in FB1's +3V3 pad: it gets its own via, just below and to the left
fp1 = at(FP['FB1'], '1')
vv = (fp1[0] - 0.46, f1[3] + 0.6)
R(fp1, (fp1[0] - 0.2, f1[3] + 0.2), vv, net='/+3V3')
v = pcbnew.PCB_VIA(b)
v.SetPosition(pcbnew.VECTOR2I(mm(OX + vv[0]), mm(OY + vv[1])))
v.SetWidth(mm(0.6))
v.SetDrill(mm(0.3))
v.SetNet(b.FindNet('/+3V3'))
v.SetLocked(True)
b.Add(v)
pcbnew.SaveBoard(sys.argv[1], b)
print('corner placed, shift %.2f %.2f' % (DX, DY))
